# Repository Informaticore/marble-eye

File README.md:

# Marble Eye
Marble Eye is an IR pass through Sensor for a project I am working on. It can detect objects which are passing by at a distance with up to 2cm.

# Marble Eye Hub
The Marble Eye Hub is a GPIO-Expander with 16 Ports to connect up to 16 Marble Eyes to it. Based on interrupts the Hub can detect pass through on all 16 channels.

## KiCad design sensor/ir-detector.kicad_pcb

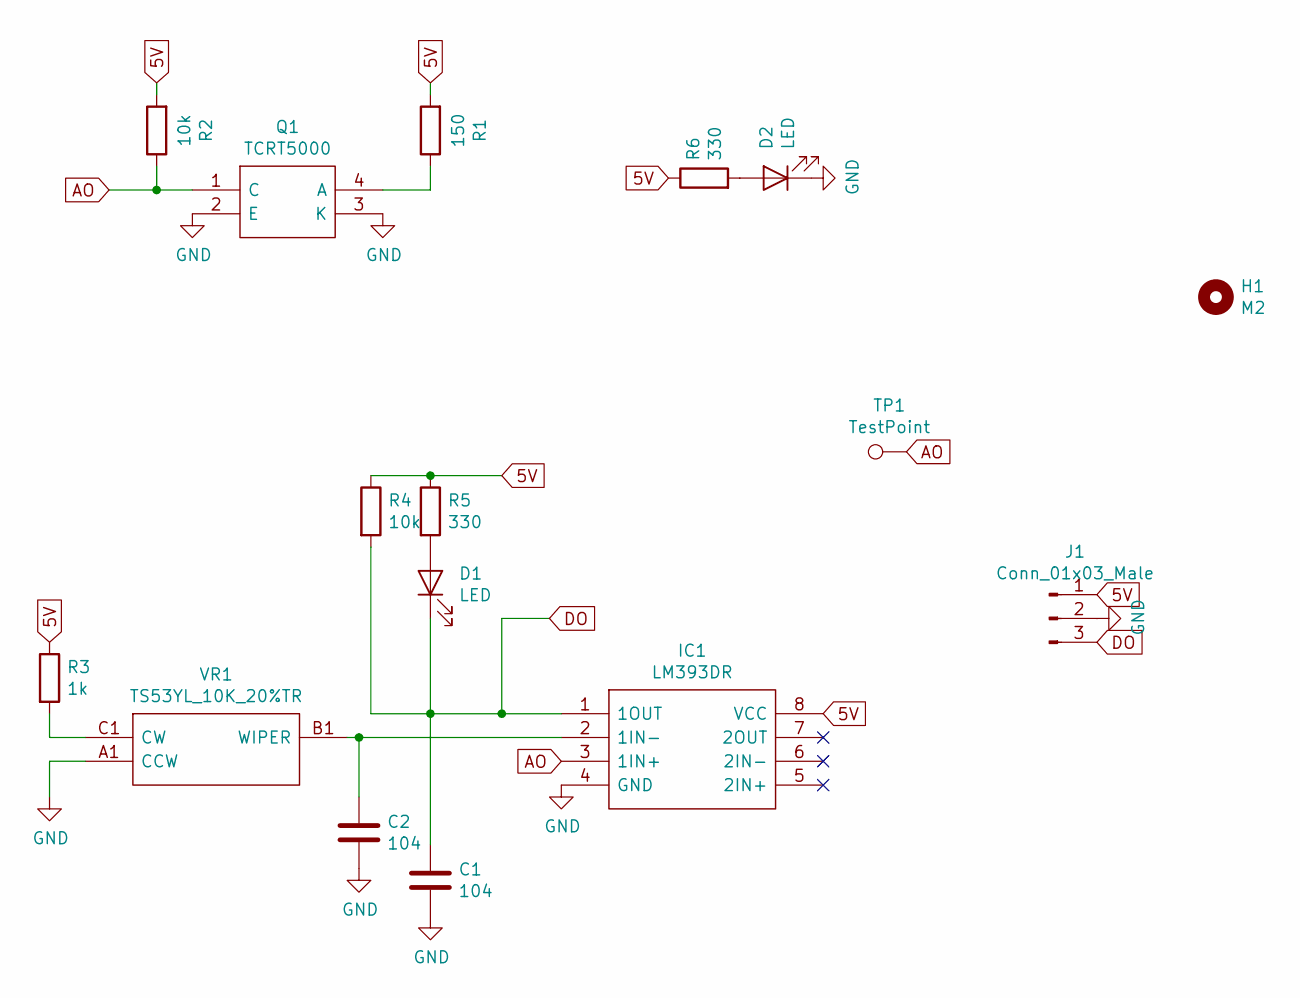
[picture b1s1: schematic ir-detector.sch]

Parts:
C1, C2: 104; C_0603
D1, D2: LED; LED_0603
H1: M2; MountingHole_2.2mm_M2_Pad_Via
IC1: LM393DR; SOIC127P600X175-8N; Manufacturer_Part_Number LM393DR; Mouser Part Number 595-LM393DR
J1: Conn_01x03_Male; JST_PH_S3B-PH-K_03x2.00mm_Angled
Q1: TCRT5000; Manufacturer_Part_Number TCRT5000; Mouser Part Number 782-TCRT5000
R1: 150; R_0603
R2, R4: 10k; R_0603
R3: 1k; R_0603
R5, R6: 330; R_0603
TP1: TestPoint; Measurement_Point_Round-SMD-Pad_Small
VR1: TS53YL_10K_20%TR; TS53YL204MR10; Manufacturer_Part_Number TS53YL 10K 20%TR; Mouser Part Number 75-TS53YL10K20%TR

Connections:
5V: IC1.8 (VCC), J1.1, R1.2, R2.2, R3.1, R4.1, R5.1, R6.1
AO: IC1.3 (1IN+), Q1.1 (C), R2.1, TP1.1
DO: C1.1, D1.1 (K), IC1.1 (1OUT), J1.3, R4.2
GND: C1.2, C2.2, D2.1 (K), IC1.4 (GND), J1.2, Q1.2 (E), Q1.3 (K), VR1.A1 (CCW)
unnamed: C2.1, IC1.2 (1IN-), VR1.B1 (WIPER)
unnamed: D1.2 (A), R5.2
unnamed: D2.2 (A), R6.2
unnamed: Q1.4 (A), R1.1
unnamed: R3.2, VR1.C1 (CW)

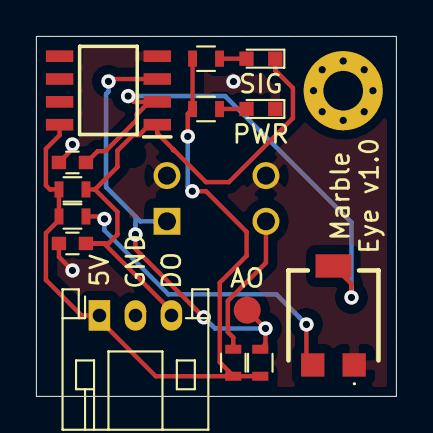
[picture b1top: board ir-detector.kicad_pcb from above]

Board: 2 copper layers, 20.0 x 20.0 mm, 16 parts (1 on the bottom side), 9 nets.

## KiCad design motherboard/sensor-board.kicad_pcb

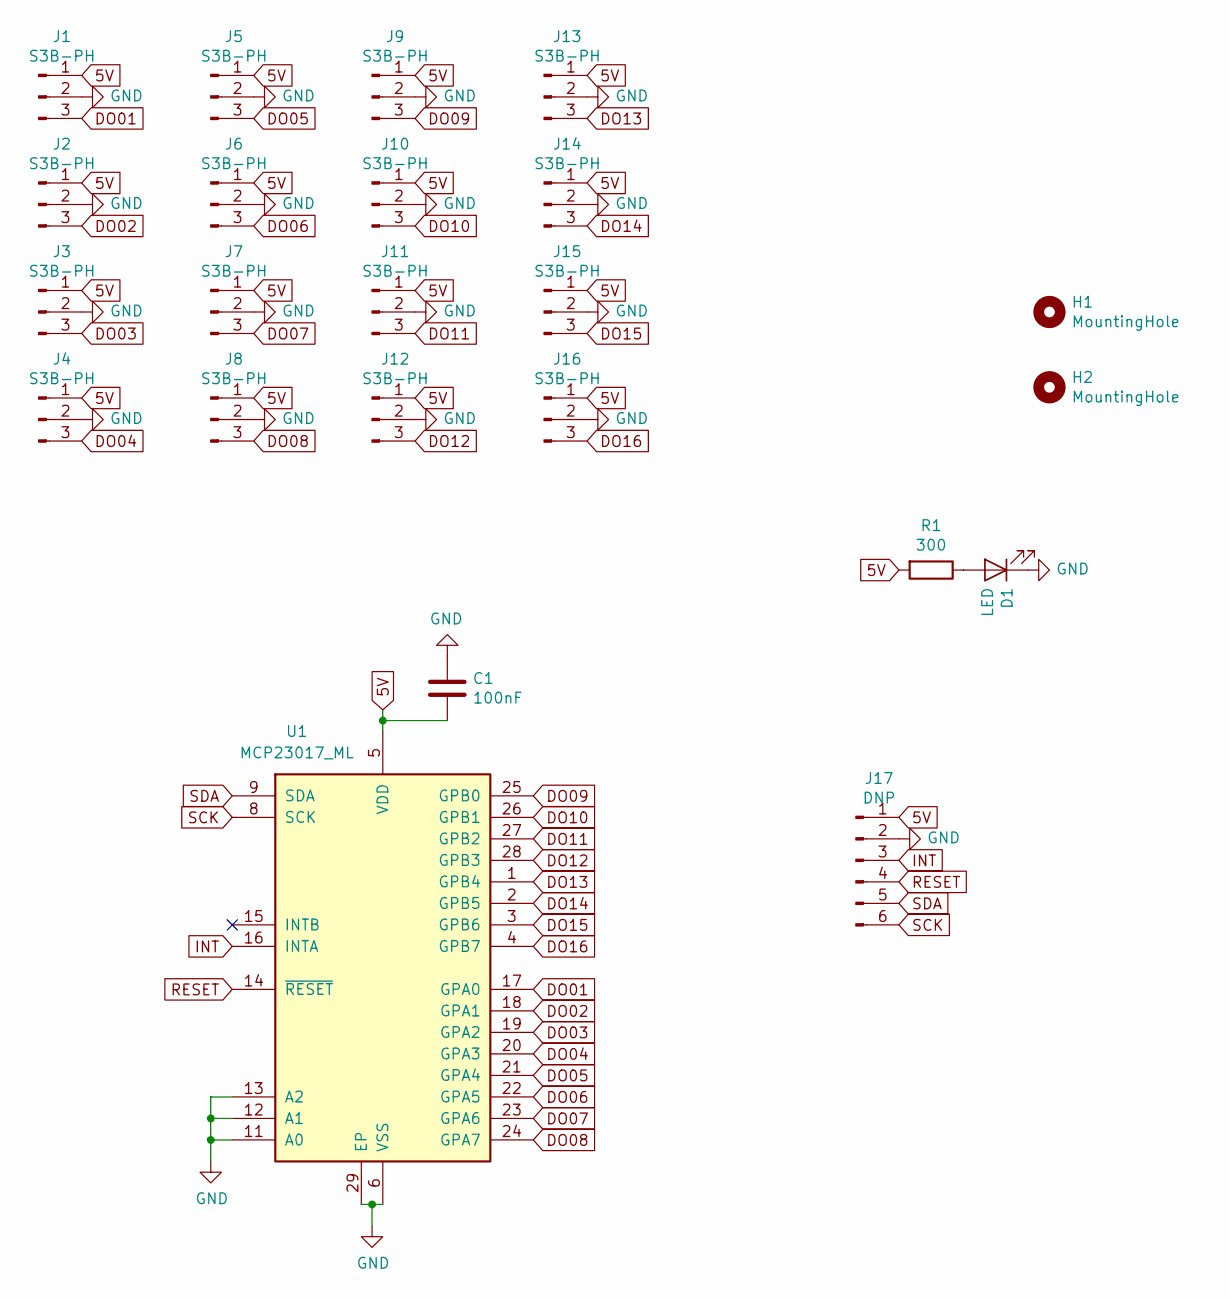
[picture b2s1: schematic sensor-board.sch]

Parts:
C1: 100nF; C_0603
D1: LED; LED_0603
H1, H2: MountingHole; MountingHole_3mm_Pad_Via
J1, J2, J3, J4, J5, J6, J7, J8, J9, J10, J11, J12, J13, J14, J15, J16: S3B-PH; JST_PH_S3B-PH-K_03x2.00mm_Angled
J17: DNP; PinSocket_1x06_P2.54mm_Vertical
R1: 300; R_0603
U1: MCP23017_ML; QFN65P600X600X100-29N-D

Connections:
5V: C1.2, J1.1, J2.1, J3.1, J4.1, J5.1, J6.1, J7.1, J8.1, J9.1, J10.1, J11.1, J12.1, J13.1, J14.1, J15.1, J16.1, J17.1, R1.2, U1.5 (VDD)
DO01: J1.3, U1.17 (GPA0)
DO02: J2.3, U1.18 (GPA1)
DO03: J3.3, U1.19 (GPA2)
DO04: J4.3, U1.20 (GPA3)
DO05: J5.3, U1.21 (GPA4)
DO06: J6.3, U1.22 (GPA5)
DO07: J7.3, U1.23 (GPA6)
DO08: J8.3, U1.24 (GPA7)
DO09: J9.3, U1.25 (GPB0)
DO10: J10.3, U1.26 (GPB1)
DO11: J11.3, U1.27 (GPB2)
DO12: J12.3, U1.28 (GPB3)
DO13: J13.3, U1.1 (GPB4)
DO14: J14.3, U1.2 (GPB5)
DO15: J15.3, U1.3 (GPB6)
DO16: J16.3, U1.4 (GPB7)
GND: C1.1, D1.1 (K), J1.2, J2.2, J3.2, J4.2, J5.2, J6.2, J7.2, J8.2, J9.2, J10.2, J11.2, J12.2, J13.2, J14.2, J15.2, J16.2, J17.2, U1.6 (VSS), U1.11 (A0), U1.12 (A1), U1.13 (A2), U1.29 (EP)
INT: J17.3, U1.16 (INTA)
unnamed: D1.2 (A), R1.1
RESET: J17.4, U1.14 (~RESET~)
SCK: J17.6, U1.8 (SCK)
SDA: J17.5, U1.9 (SDA)

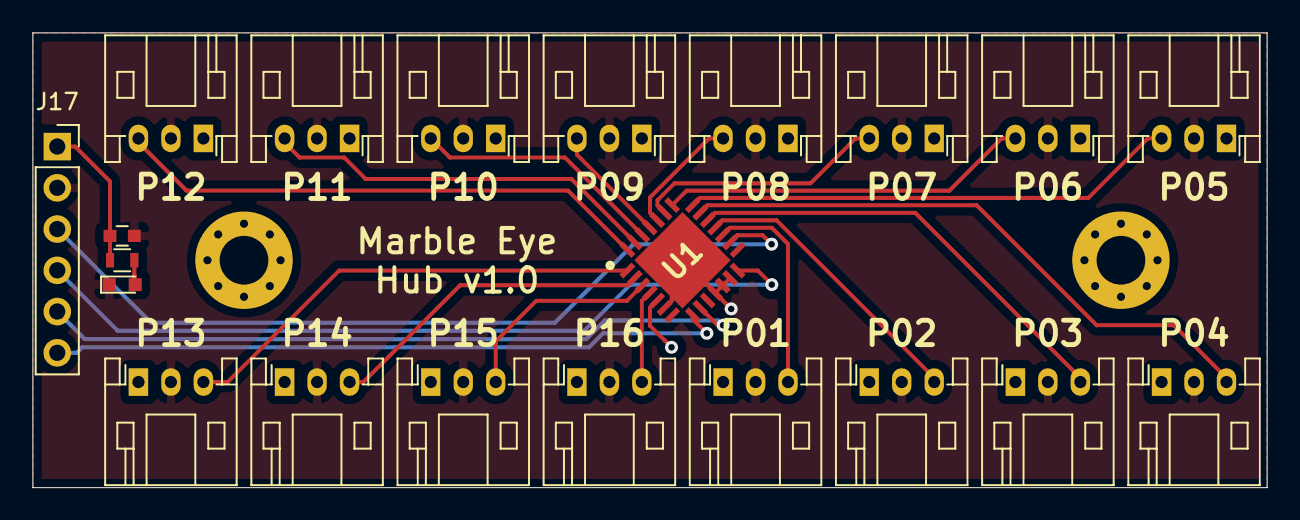
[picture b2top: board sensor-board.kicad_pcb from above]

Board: 2 copper layers, 76.0 x 28.0 mm, 23 parts (0 on the bottom side), 23 nets.
